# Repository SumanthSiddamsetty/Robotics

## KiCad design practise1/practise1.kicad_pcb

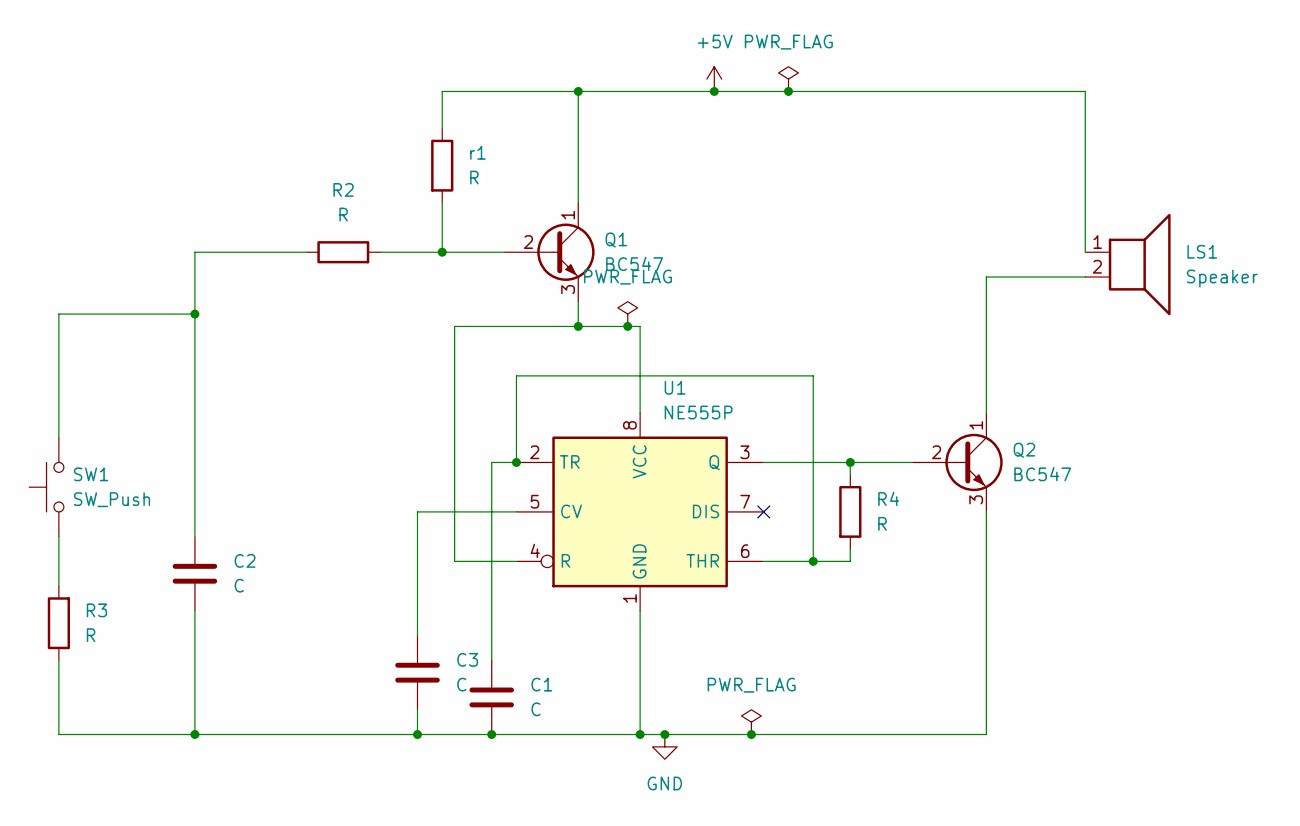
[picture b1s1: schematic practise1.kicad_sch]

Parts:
C1, C2, C3: C; C_Axial_L3.8mm_D2.6mm_P7.50mm_Horizontal
LS1: Speaker; Speaker_CUI_CMR-1206S-67
Q1, Q2: BC547; TO-92_Inline
R2, R3, R4: R; R_Axial_DIN0204_L3.6mm_D1.6mm_P1.90mm_Vertical
SW1: SW_Push; SW_PUSH-12mm_Wuerth-430476085716
U1: NE555P; DIP-8_W7.62mm
r1: R; R_Axial_DIN0204_L3.6mm_D1.6mm_P1.90mm_Vertical

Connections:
+5V: LS1.1, Q1.1 (C), r1.1
GND: C1.2, C2.2, C3.2, Q2.3 (E), R3.1, U1.1 (GND)
unnamed: C2.1, R2.1, SW1.2
unnamed: Q1.2 (B), R2.2, r1.2
unnamed: Q1.3 (E), U1.4 (R), U1.8 (VCC)
unnamed: Q2.2 (B), R4.1, U1.3 (Q)
unnamed: LS1.2, Q2.1 (C)
unnamed: R3.2, SW1.1
unnamed: C3.1, U1.5 (CV)
unnamed: C1.1, R4.2, U1.2 (TR), U1.6 (THR)

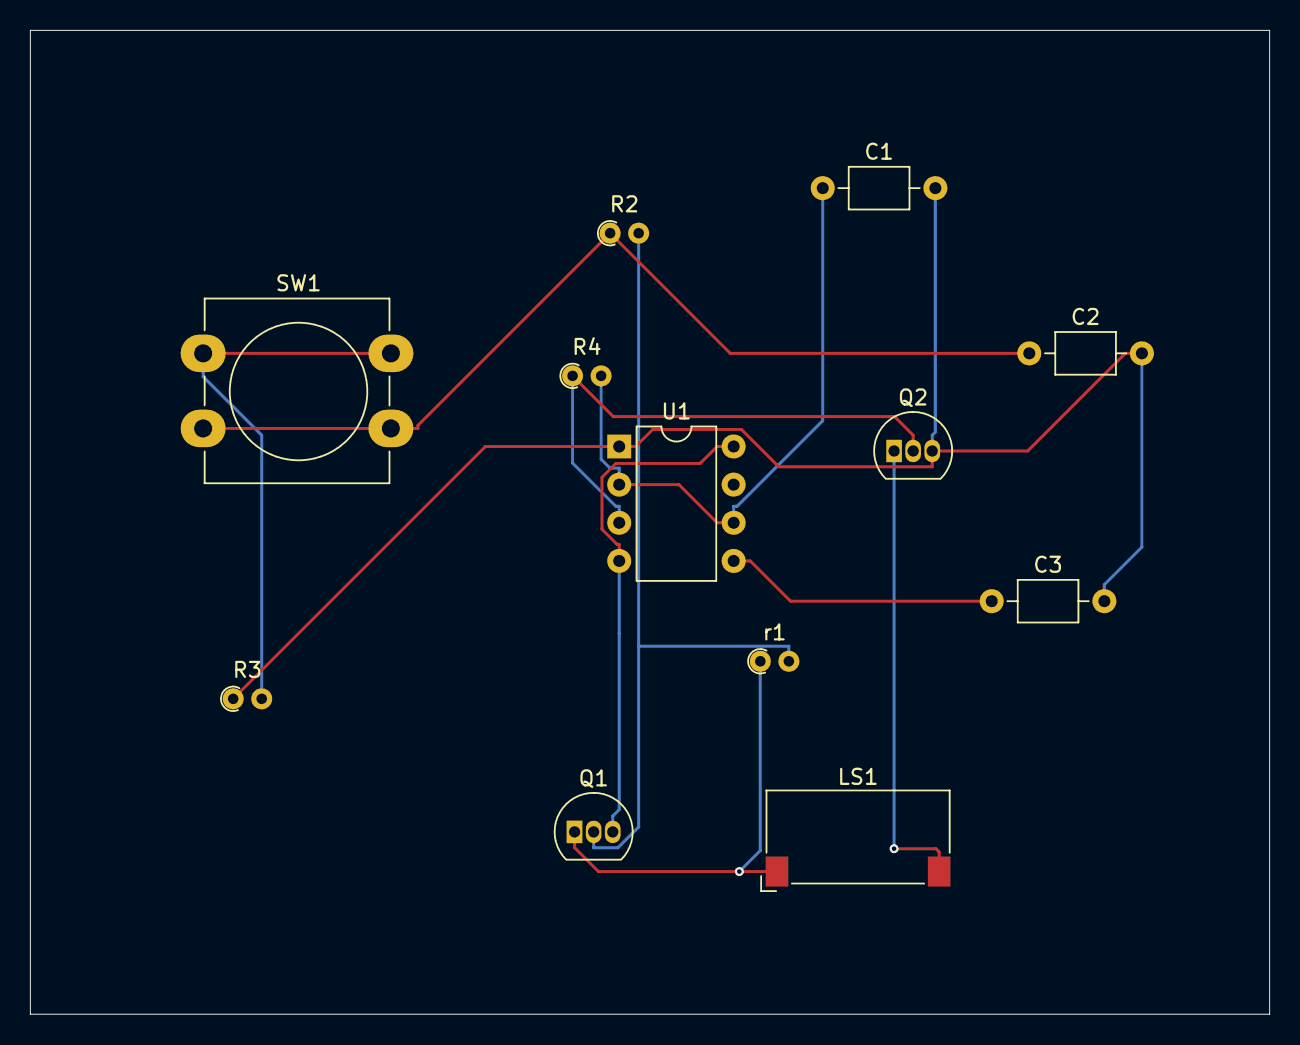
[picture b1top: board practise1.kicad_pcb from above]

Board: 2 copper layers, 82.5 x 65.5 mm, 12 parts (0 on the bottom side), 10 nets.

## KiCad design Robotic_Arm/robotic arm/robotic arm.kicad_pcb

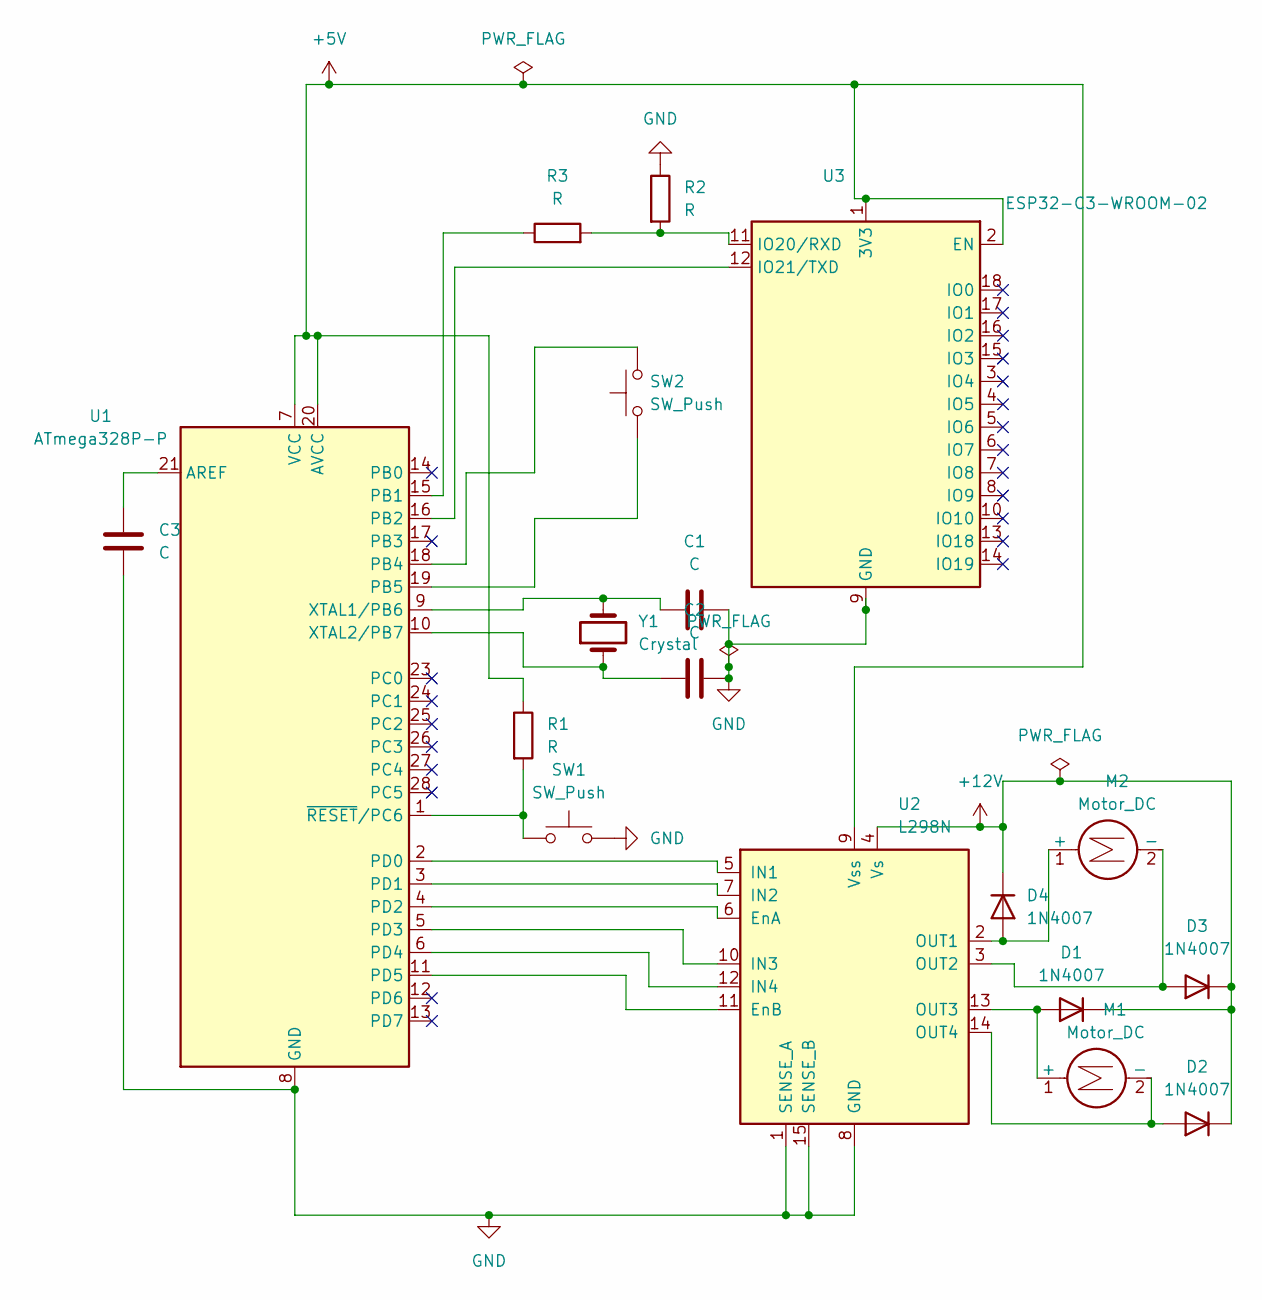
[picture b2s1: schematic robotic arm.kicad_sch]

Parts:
C1, C2, C3: C; CP_Axial_L10.0mm_D4.5mm_P15.00mm_Horizontal
D1, D2, D3, D4: 1N4007; D_DO-41_SOD81_P10.16mm_Horizontal
M1, M2: Motor_DC; Vybronics_VZ30C1T8219732L
R1, R2, R3: R; R_Axial_DIN0207_L6.3mm_D2.5mm_P5.08mm_Vertical
SW1, SW2: SW_Push; SW_PUSH_6mm_H5mm
U1: ATmega328P-P; DIP-28_W7.62mm
U2: L298N; TO-220-15_P2.54x2.54mm_StaggerOdd_Lead4.58mm_Vertical
U3: ESP32-C3-WROOM-02
Y1: Crystal; Crystal_AT310_D3.0mm_L10.0mm_Horizontal

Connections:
+5V: R1.1, U1.7 (VCC), U1.20 (AVCC), U2.9 (Vss), U3.1 (3V3), U3.2 (EN)
+12V: D1.1 (K), D2.1 (K), D3.1 (K), D4.1 (K), U2.4 (Vs)
GND: C1.1, C2.2, C3.2, R2.1, SW1.2, U1.8 (GND), U1.22 (GND), U2.1 (SENSE_A), U2.8 (GND), U2.15 (SENSE_B), U3.9 (GND), U3.19 (GND)
unnamed: D1.2 (A), M1.1 (+), U2.13 (OUT3)
unnamed: D2.2 (A), M1.2 (-), U2.14 (OUT4)
unnamed: D3.2 (A), M2.2 (-), U2.3 (OUT2)
unnamed: D4.2 (A), M2.1 (+), U2.2 (OUT1)
unnamed: C3.1, U1.21 (AREF)
unnamed: R3.1, U1.15 (PB1)
unnamed: U1.16 (PB2), U3.12 (IO21/TXD)
unnamed: SW2.2, U1.18 (PB4)
unnamed: SW2.1, U1.19 (PB5)
unnamed: U1.2 (PD0), U2.5 (IN1)
unnamed: U1.3 (PD1), U2.7 (IN2)
unnamed: U1.4 (PD2), U2.6 (EnA)
unnamed: U1.5 (PD3), U2.10 (IN3)
unnamed: U1.6 (PD4), U2.12 (IN4)
unnamed: U1.11 (PD5), U2.11 (EnB)
unnamed: C1.2, U1.9 (XTAL1/PB6), Y1.2
unnamed: C2.1, U1.10 (XTAL2/PB7), Y1.1
unnamed: R1.2, SW1.1, U1.1 (~RESET/PC6)
unnamed: R2.2, R3.2, U3.11 (IO20/RXD)

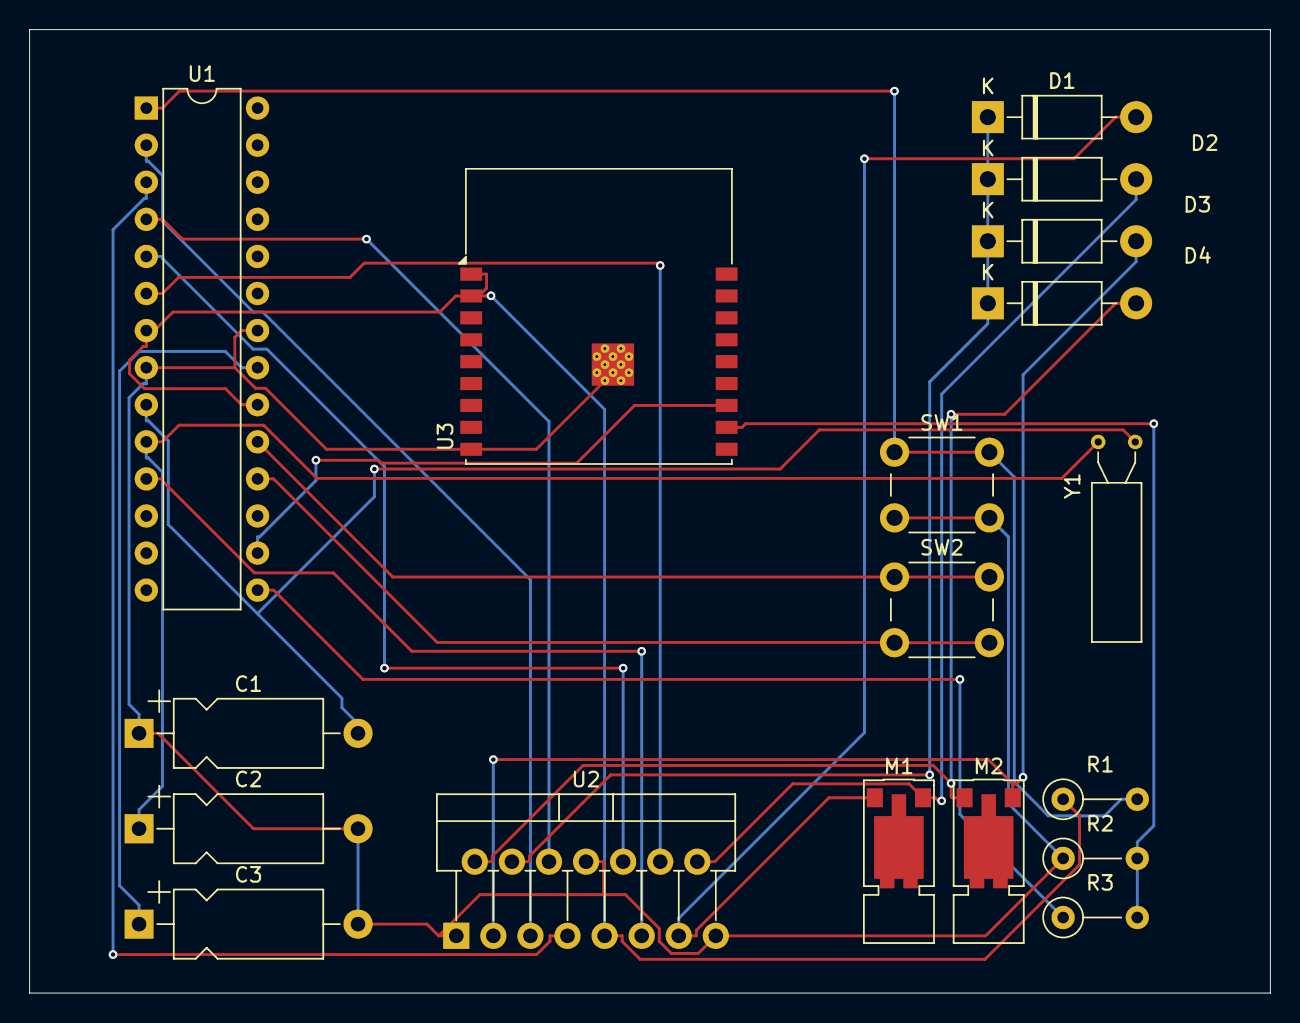
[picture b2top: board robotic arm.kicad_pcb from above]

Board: 2 copper layers, 85.0 x 66.0 mm, 18 parts (0 on the bottom side), 22 nets.

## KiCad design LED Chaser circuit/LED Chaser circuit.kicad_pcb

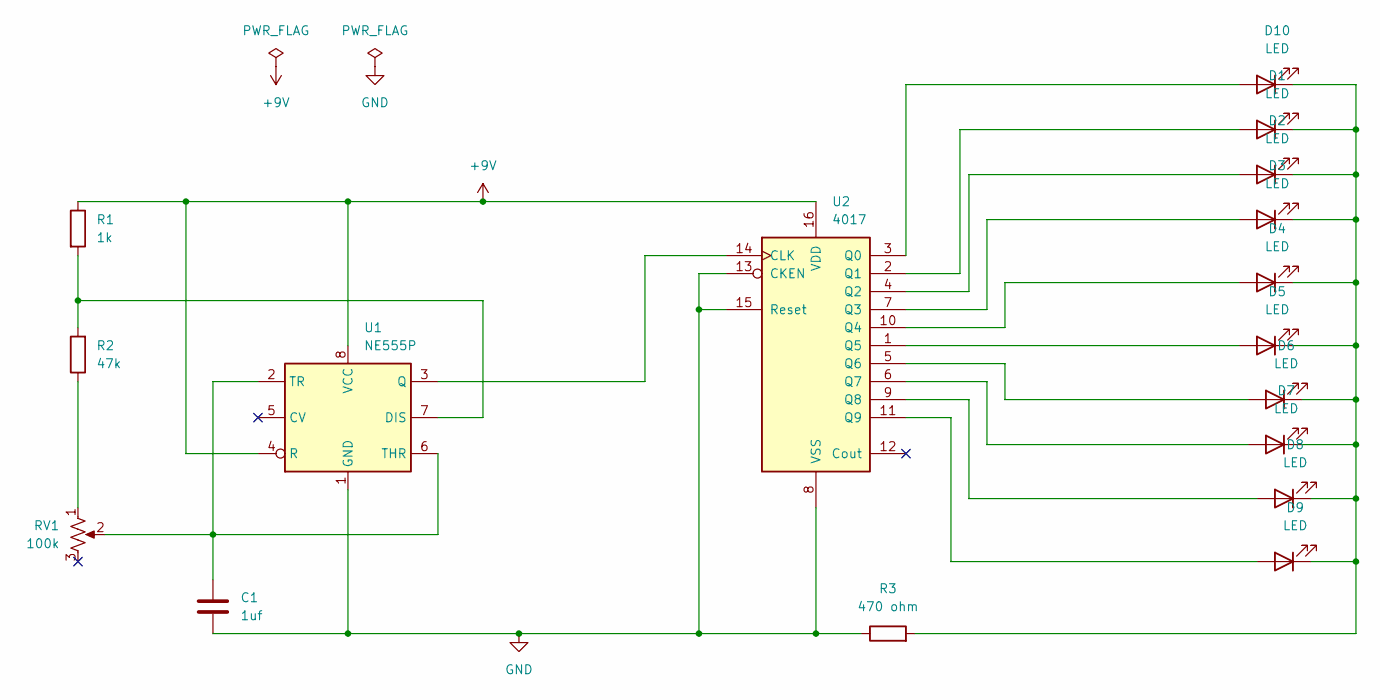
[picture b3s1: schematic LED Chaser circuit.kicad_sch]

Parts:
C1: 1uf; CP_Radial_D4.0mm_P2.00mm
D1, D2, D3, D4, D5, D6, D7, D8, D9, D10: LED; LED_D3.0mm
R1: 1k; R_Axial_DIN0204_L3.6mm_D1.6mm_P5.08mm_Horizontal
R2: 47k; R_Axial_DIN0204_L3.6mm_D1.6mm_P5.08mm_Horizontal
R3: 470 ohm; R_Axial_DIN0204_L3.6mm_D1.6mm_P5.08mm_Horizontal
RV1: 100k; Potentiometer_Bourns_3386W_Horizontal
U1: NE555P; DIP-8_W7.62mm
U2: 4017; DIP-16_W7.62mm

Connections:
+9V: R1.1, U1.4 (R), U1.8 (VCC), U2.16 (VDD)
GND: C1.2, R3.1, U1.1 (GND), U2.8 (VSS), U2.13 (CKEN), U2.15 (Reset)
unnamed: D1.2 (A), U2.2 (Q1)
unnamed: D1.1 (K), D2.1 (K), D3.1 (K), D4.1 (K), D5.1 (K), D6.1 (K), D7.1 (K), D8.1 (K), D9.1 (K), D10.1 (K), R3.2
unnamed: D2.2 (A), U2.4 (Q2)
unnamed: D3.2 (A), U2.7 (Q3)
unnamed: D4.2 (A), U2.10 (Q4)
unnamed: D5.2 (A), U2.1 (Q5)
unnamed: D6.2 (A), U2.5 (Q6)
unnamed: D7.2 (A), U2.6 (Q7)
unnamed: D8.2 (A), U2.9 (Q8)
unnamed: D9.2 (A), U2.11 (Q9)
unnamed: D10.2 (A), U2.3 (Q0)
unnamed: R2.1, RV1.1
unnamed: R1.2, R2.2, U1.7 (DIS)
unnamed: U1.3 (Q), U2.14 (CLK)
unnamed: C1.1, RV1.2, U1.2 (TR), U1.6 (THR)

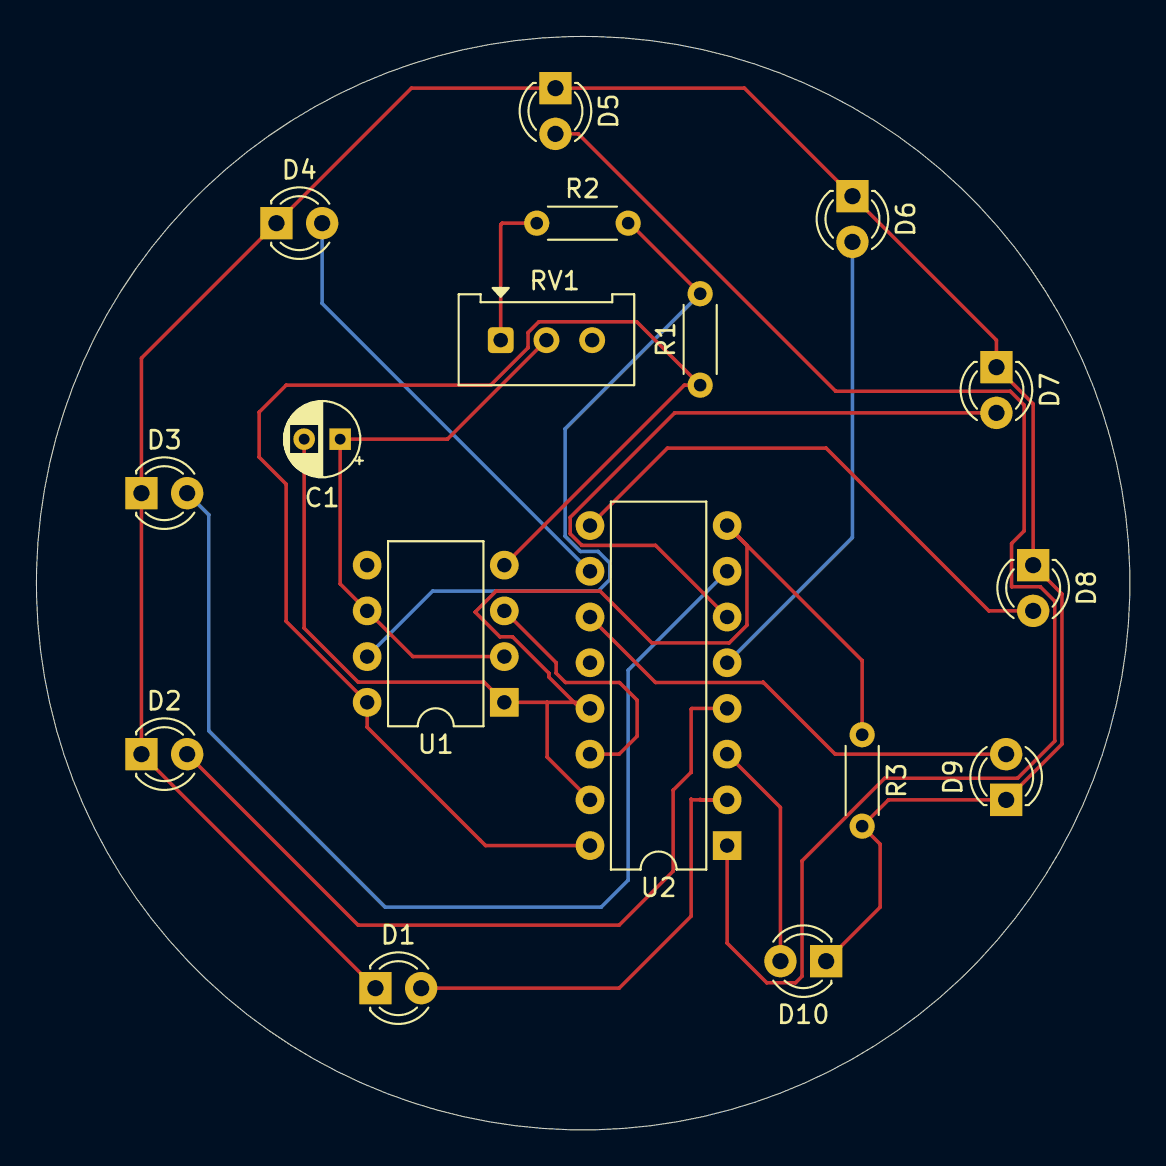
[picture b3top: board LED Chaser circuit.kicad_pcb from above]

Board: 2 copper layers, 60.7 x 60.7 mm, 17 parts (0 on the bottom side), 17 nets.

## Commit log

2025-06-26 first
2025-06-26 Second commit
2025-06-26 LED Chaser
2025-06-26 practic
2025-06-26 Servo
2025-06-26 Done!
2025-07-10 Webot
2025-07-10 Robotic_Maze
    It is a robotic maze.
    The robot can be controlled through the Keyboard, Websocket, Raspberry...
    IT is a very easy and simple project to understand robotics in webot R2025a.
2025-07-17 Pick_Place
    It is a Robotic ARM u can use it throught Demo/ keyboard/ Websocket/
    And the complete simulation is used in the webots R2025a version i request to use the same version to simulate it
